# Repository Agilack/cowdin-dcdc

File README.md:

Cowdin DC/DC module
===================

This project is a DC/DC power supply module with a form-factor compatible with
IEC/EN 60715 enclosures (1 unit width). The output voltage is not variable but
it is possible to have different values with this design, by modifying value
of some components.

<table>
<tr><td>
<b>Specifications:</b>
<ul>
  <li>Input voltage:<ul>
    <li>Version 40: 0V -> 36V</li>
    <li>Version 60: 0V -> 48V</li>
  </ul></li>
  <li>Output voltage:<ul>
    <li>Stadard versions : 3,3V / 5V / 12V / 24V</li>
    <li>Custom version: any value from 0V to VIn</li>
  </ul></li>
  <li>Output current : up to 1V</li>
</ul>
</td>
<td>

</td>
</tr>
</table>

Sources
-------

This board has been designed using KiCad EDA (version 5). All sources files
(schematics, routing, ...) are available into the `prj-kicad` folder. You can
re-use this design under terms of the Creative Commons ShareAlike license
(CC BY-SA)

<table>
<tr>
<td></td>
<td></td>
</tr>
<tr>
<td>Fig1: Preview of the KiCad schematics</td>
<td>Fig2: Preview of the KiCad routing</td>
</tr>
</table>

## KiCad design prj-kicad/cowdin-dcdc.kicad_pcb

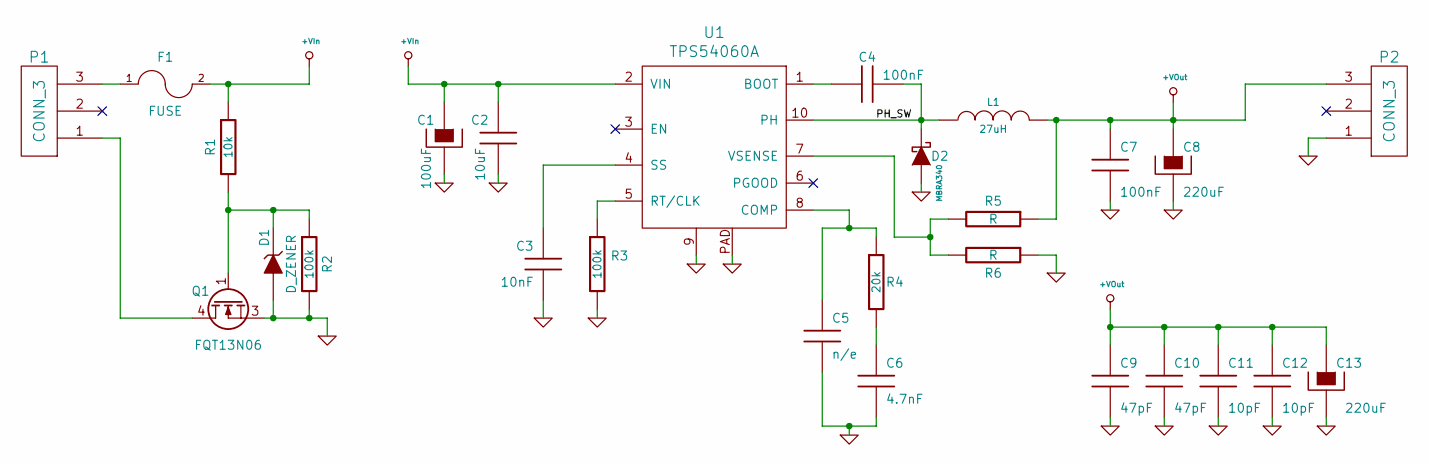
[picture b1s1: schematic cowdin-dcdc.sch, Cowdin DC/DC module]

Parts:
C1: 100uF; C_ALU_8x10.5
C2: 10uF; SMD1206
C3: 10nF; SMD0603
C4, C7: 100nF; SMD0603
C5: n/e; SMD0603
C6: 4.7nF; SMD0603
C8, C13: 220uF; C_TPB_D4
C9, C10: 47pF; SMD0603
C11, C12: 10pF; SMD0603
D1: D_ZENER; SOD323
D2: MBRA340; DO214AC
F1: FUSE; F_2920Lx
L1: 27uH; I_MSS1048
P1, P2: CONN_3; CONN_MC000035
Q1: FQT13N06; SOT223
R1: 10k; SMD0603
R2, R3: 100k; SMD0603
R4: 20k; SMD0603
R5, R6: R; SMD0603
U1: TPS54060A; MSOP10p

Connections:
/PH_SW: C4.2, D2.2 (K), L1.1, U1.10 (PH)
GND: C1.2, C2.2, C3.2, C5.2, C6.2, C7.2, C8.2, C9.2, C10.2, C11.2, C12.2, C13.2, D1.1 (A), D2.1 (A), P2.1, Q1.3 (S), R2.2, R3.2, R6.1, U1.9, U1.PAD
unnamed: C3.1, U1.4 (SS)
unnamed: C4.1, U1.1 (BOOT)
unnamed: C5.1, R4.1, U1.8 (COMP)
unnamed: C6.1, R4.2
unnamed: D1.2 (K), Q1.1 (G), R1.2, R2.1
unnamed: F1.1, P1.3
unnamed: P1.1, Q1.4 (D)
unnamed: R3.1, U1.5 (RT/CLK)
unnamed: R5.2, R6.2, U1.7 (VSENSE)
VIn: C1.1, C2.1, F1.2, R1.1, U1.2 (VIN)
VOut: C7.1, C8.1, C9.1, C10.1, C11.1, C12.1, C13.1, L1.2, P2.3, R5.1

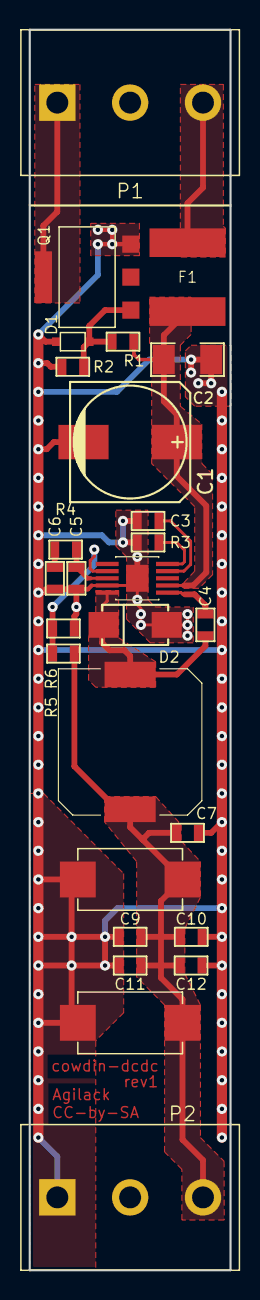
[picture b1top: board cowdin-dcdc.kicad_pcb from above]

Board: 2 copper layers, 14.0 x 86.5 mm, 27 parts (0 on the bottom side), 13 nets.

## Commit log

2020-03-25 = ADD: Create project, add schematics and routing
2020-03-26 = ADD: Create production files for rev1
2020-04-11 = ADD: Insert pictures of the first PCB, improve readme file

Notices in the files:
prj-kicad/cowdin-dcdc.kicad_pcb:
License: Creative Commons CC-by-SA
